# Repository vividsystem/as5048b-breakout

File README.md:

# AS5048B Breakout Board

> [!NOTE]
> This is a breakout for the AS5048B not AS5048A board i.e. this is a breakout for the I²C version.

## Specs & Features 
- 14bit resolution -> 16384 positions per revolution
- I²C High Speed at 3.4MHz clock frequency
- easy hand-assembly
- JST SM04B-SRSS (SH series) connector for easy connections
(SparkFun Qwiic/Adafruit STEMMA QT/Arduino Modulino compatible)

## Usage
### Choosing the correct magnet
* 6-8mm diameter
* \>= 2.5mm height
* diametric

### Magnet Placement
* 0.5mm to 2.5mm above IC
* magnet and board share same center (displacement of up to 0.25mm ok)

more details [here](https://look.ams-osram.com/m/287d7ad97d1ca22e/original/AS5048-DS000298.pdf)

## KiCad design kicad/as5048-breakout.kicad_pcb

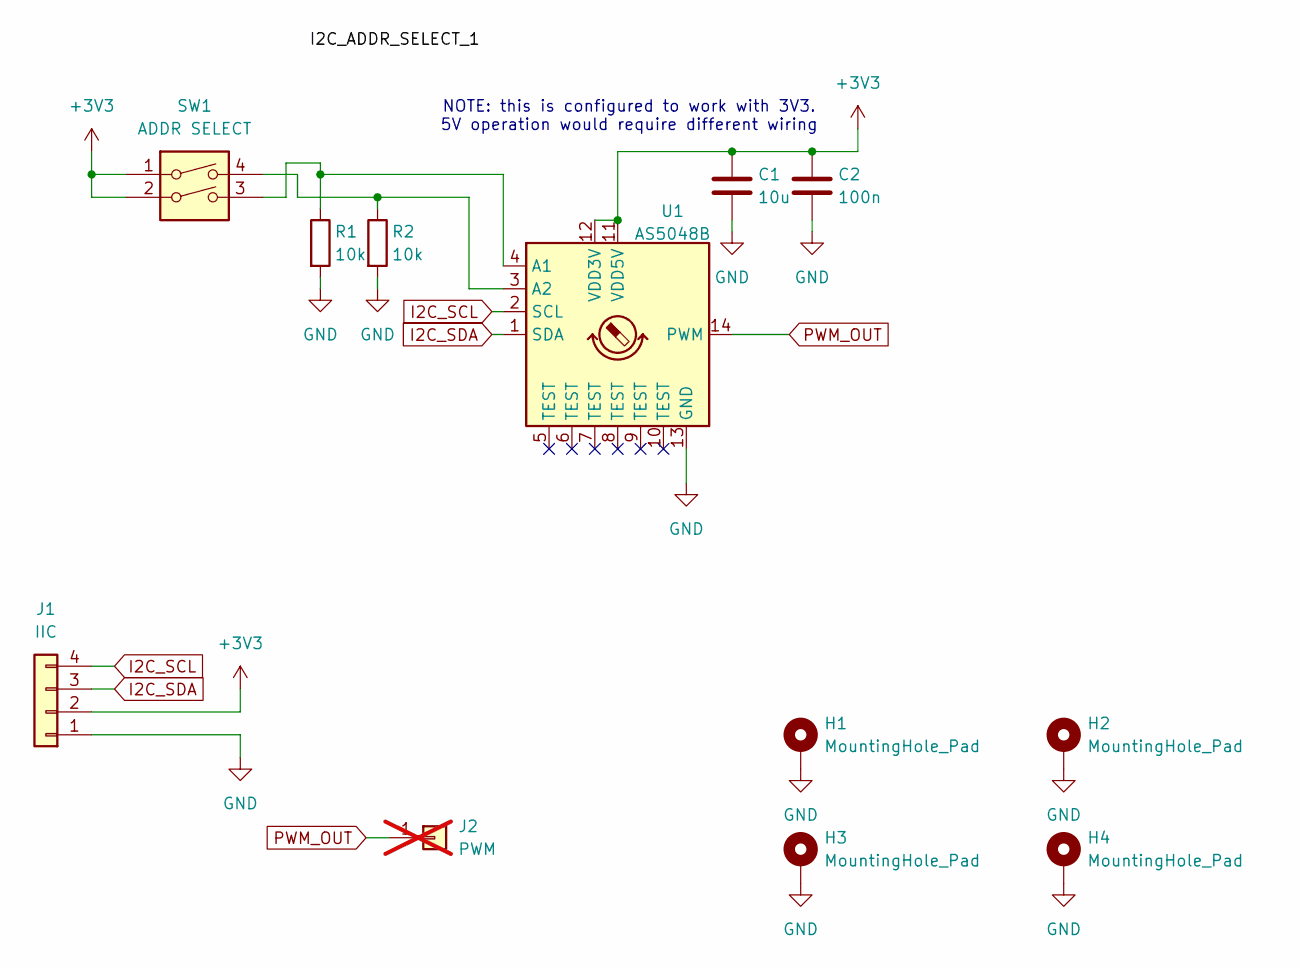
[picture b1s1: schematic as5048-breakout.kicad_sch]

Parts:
C1: 10u; C_0805_2012Metric; LCSC Part C15850
C2: 100n; C_0805_2012Metric; LCSC Part C28233
H1, H2, H3, H4: MountingHole_Pad; MountingHole_2.2mm_M2_DIN965_Pad
J1: IIC; JST_SH_SM04B-SRSS-TB_1x04-1MP_P1.00mm_Horizontal; LCSC Part C160404
J2: PWM; SolderWirePad_1x01_SMD_1x2mm; not fitted
R1, R2: 10k; R_0603_1608Metric; LCSC Part C25804
SW1: ADDR SELECT; EP-02KS DIP 1.27mm; LCSC Part C54949
U1: AS5048B; TSSOP-14_4.4x5mm_P0.65mm; LCSC Part C2655184

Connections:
+3V3: C1.2, C2.2, J1.2, SW1.1, SW1.2, U1.11 (VDD5V), U1.12 (VDD3V)
GND: C1.1, C2.1, H1.1, H2.1, H3.1, H4.1, J1.1, R1.2, R2.2, U1.13 (GND)
I2C_SCL: J1.4, U1.2 (SCL)
I2C_SDA: J1.3, U1.1 (SDA)
unnamed: R1.1, SW1.3, U1.4 (A1)
unnamed: R2.1, SW1.4, U1.3 (A2)
PWM_OUT: J2.1, U1.14 (PWM)

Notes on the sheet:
NOTE: this is configured to work with 3V3. 5V operation would require different wiring

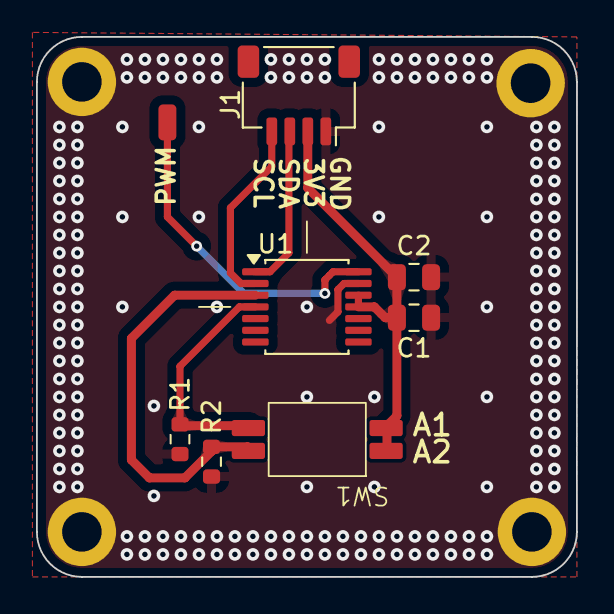
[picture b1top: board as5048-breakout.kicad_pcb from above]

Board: 2 copper layers, 30.0 x 30.0 mm, 12 parts (0 on the bottom side), 7 nets.

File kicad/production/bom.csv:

Designator,Footprint,Quantity,Value,LCSC Part #
C1,0805,1,10u,C15850
C2,0805,1,100n,C28233
J1,JST_SH_SM04B-SRSS-TB_1x04-1MP_P1.00mm_Horizontal,1,IIC,C160404
"R1, R2",0603,2,10k,C25804
SW1,EP-02KS DIP 1.27mm,1,ADDR SELECT,C54949
U1,TSSOP-14_4.4x5mm_P0.65mm,1,AS5048B,C2655184

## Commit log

2026-02-26 docs: add specs and usage
2026-02-26 fix: bom LCSC part no
2026-02-26 docs: fix note
2026-02-26 docs: add pcb render image
2026-02-26 Fix image rendering in README and clarify note
2026-02-26 docs: fix formatting of >=
2026-03-02 finalizing this
2026-05-18 feat: change pinheader to JST SH 1x4
    with same pinouts as the Adafruit Qwiic or Stemma
    connectors so that they could be used with their boards
    (different pitch connectors used)
2026-05-18 docs: add note about connector
2026-05-18 chore: update note to include all vendors using JST SH connectors
2026-05-18 docs: update image to v2
